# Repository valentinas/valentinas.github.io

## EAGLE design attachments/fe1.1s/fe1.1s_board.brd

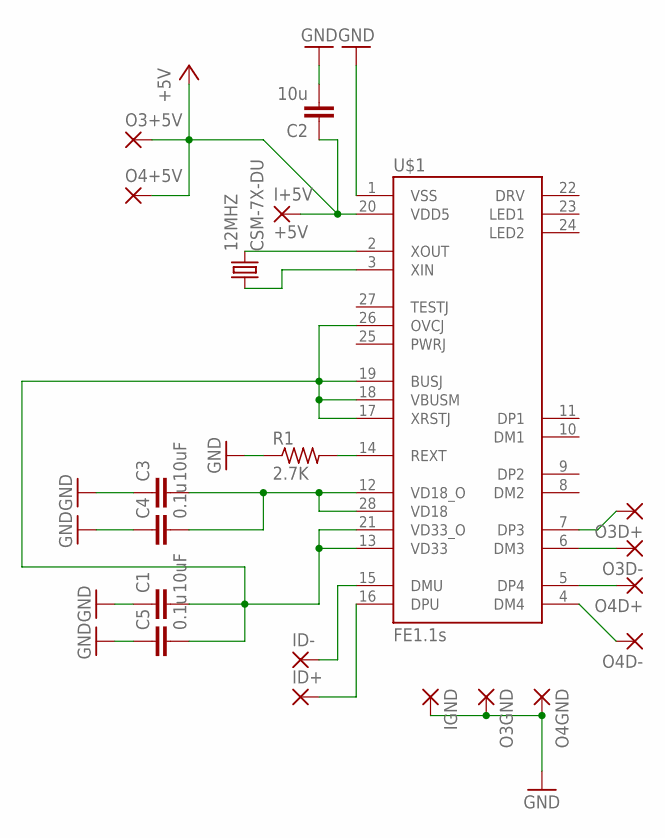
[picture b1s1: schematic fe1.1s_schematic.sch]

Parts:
12MHZ: CSM-7X-DU
C1, C3: 10uF; C0603
C2: 10u; C0603
C4, C5: 0.1u; C0603
I+5V: +5V; 1,6/0,8
ID+: 1,6/0,8
ID-: 1,6/0,8
IGND: 1,6/0,8
O3+5V, O3D+, O3D-, O3GND, O4+5V, O4D+, O4D-, O4GND: 1,6/0,8
R1: 2.7K; R0603
U$1: FE1.1S; FE1.1S_SSOP-28

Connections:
+5V: C2.1, I+5V.1, O3+5V.1, O4+5V.1, U$1.20 (VDD5)
GND: C1.1, C2.2, C3.1, C4.1, C5.1, IGND.1, O3GND.1, O4GND.1, R1.1, U$1.1 (VSS)
unnamed: 12MHZ.2, U$1.2 (XOUT)
unnamed: 12MHZ.1, U$1.3 (XIN)
unnamed: O4D-.1, U$1.4 (DM4)
unnamed: O4D+.1, U$1.5 (DP4)
unnamed: O3D+.1, U$1.7 (DP3)
unnamed: O3D-.1, U$1.6 (DM3)
unnamed: R1.2, U$1.14 (REXT)
unnamed: ID-.1, U$1.15 (DMU)
unnamed: ID+.1, U$1.16 (DPU)
unnamed: C3.2, C4.2, U$1.12 (VD18_O), U$1.28 (VD18)
unnamed: C1.2, C5.2, U$1.13 (VD33), U$1.17 (XRSTJ), U$1.18 (VBUSM), U$1.19 (BUSJ), U$1.21 (VD33_O), U$1.26 (OVCJ)

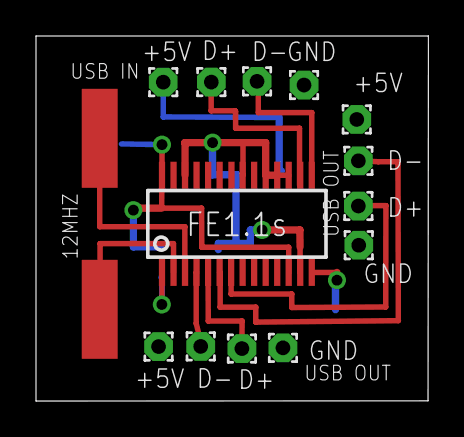
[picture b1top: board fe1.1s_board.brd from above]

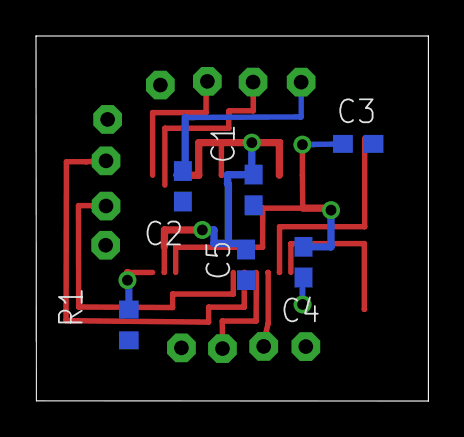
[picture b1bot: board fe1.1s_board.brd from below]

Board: 2 copper layers, 21.8 x 20.3 mm, 20 parts (6 on the bottom side), 13 nets.

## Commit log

2015-07-24 Replace master branch with page content via GitHub
2015-07-24 adding cname file to enable custom domain
2015-07-27 converting to static html
2015-07-27 ignore DS_Store bullshit
2015-07-27 add FE1.1s design
2016-02-04 Owasp CSP slides
2017-05-07 Set theme jekyll-theme-minimal
2017-05-07 test
2017-05-07 creating menu
2017-05-07 ok, I think I got it now
2017-05-07 maybe this will help
2017-05-08 removing old index
2017-05-08 gitignore + gemfile
2017-05-15 redo the FE USB hub page
2017-05-15 moving to posts, fixing index
2017-05-15 turning it into a proper jekyll blog
2017-06-14 add ga
2018-06-28 add post about fermenting
2018-07-14 updade description, fix some spelling and fermentation stuff
2018-08-18 updated fermenting post
2018-11-21 bbq sauce
2018-11-21 fixing file name
2018-11-21 add missing dash
2018-11-24 Hearty sauerkraut soup recipe
2018-11-24 rewrite sauerkraut ferminting as a recipe
2018-11-24 spell check
2018-11-24 rename sauerkraut
2018-11-26 steps to create and schedule systemd service
2018-11-26 its a timer
2019-03-15 adding slow cooked beef cheeks recipe
2019-06-25 Orange cake recipe
2019-12-23 initial commit of packing checklist
2020-05-13 adding a couple of items that I was missing on last trip
2020-05-17 update title and add firearm license and reminder to clean the gun
2020-07-06 add a couple of items to the cheklis and add a button to reset everything
2020-07-06 add a link to packing checklist
2021-04-14 add gopro
2022-04-29 Update packing_checklist.html
    Add big black rubbish bag, for things like wrapping a stag head, or other random uses.
2025-04-04 Add a few missing items
